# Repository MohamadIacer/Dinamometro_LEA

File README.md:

# Dinamometro_LEA
Repositório de desenvolvimento do sistema de dinamometria para turbinas em escala, utilizado pelo Laboratório de Energia e Ambiente da Universidade de Brasília.

Link com arquivos SolidWorks da montagem mecânica e peças individuais: https://1drv.ms/u/c/2880bb215aad6797/IQDlmrM-lfSOQbhDQPYtA1VkAWzMAm86arUpSsEFtpBo3BE?e=ooj1fM

Link com PDF do relatório da última iteração de desenvolvimento: https://1drv.ms/b/c/2880bb215aad6797/IQATOKx8Zu7TSKCGMIeG2nDvAc81WT-9CV8OO6a27Ivx5ow?e=Kimnmw

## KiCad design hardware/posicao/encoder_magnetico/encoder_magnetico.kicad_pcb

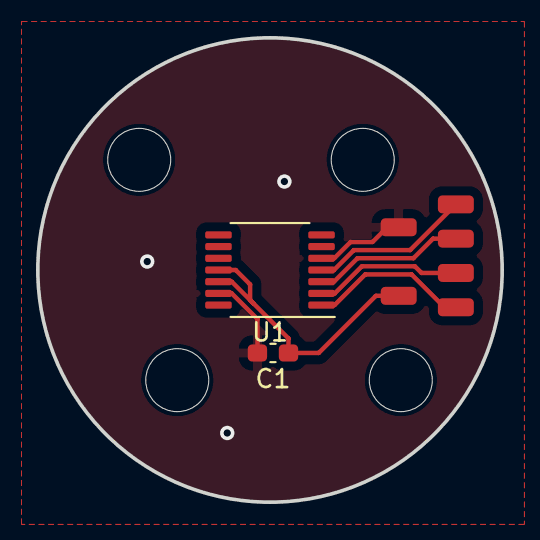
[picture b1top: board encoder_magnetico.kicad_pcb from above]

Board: 2 copper layers, 25.8 x 25.8 mm, 12 parts (0 on the bottom side), 6 nets.

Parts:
3V3: Conn_01x01; SolderWirePad_1x01_SMD_1x2mm
C1: 100nF; C_0603_1608Metric_Pad1.08x0.95mm_HandSolder
CK: Conn_01x01; SolderWirePad_1x01_SMD_1x2mm
CS: Conn_01x01; SolderWirePad_1x01_SMD_1x2mm
GND: Conn_01x01; SolderWirePad_1x01_SMD_1x2mm
H1, H2, H3, H4: MountingHole; MountingHole_3.5mm
MI: Conn_01x01; SolderWirePad_1x01_SMD_1x2mm
MO: Conn_01x01; SolderWirePad_1x01_SMD_1x2mm
U1: AS5047D; TSSOP-14_4.4x5mm_P0.65mm

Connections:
3v3: 3V3.1, C1.1, U1.11 (VDD), U1.12 (VDD3V3)
CLK: CK.1, U1.2 (CLK)
CS: CS.1, U1.1 (~CS)
GND: C1.2, GND.1, U1.5 (TST), U1.13 (GND)
MISO: MI.1, U1.3 (MISO)
MOSI: MO.1, U1.4 (MOSI)

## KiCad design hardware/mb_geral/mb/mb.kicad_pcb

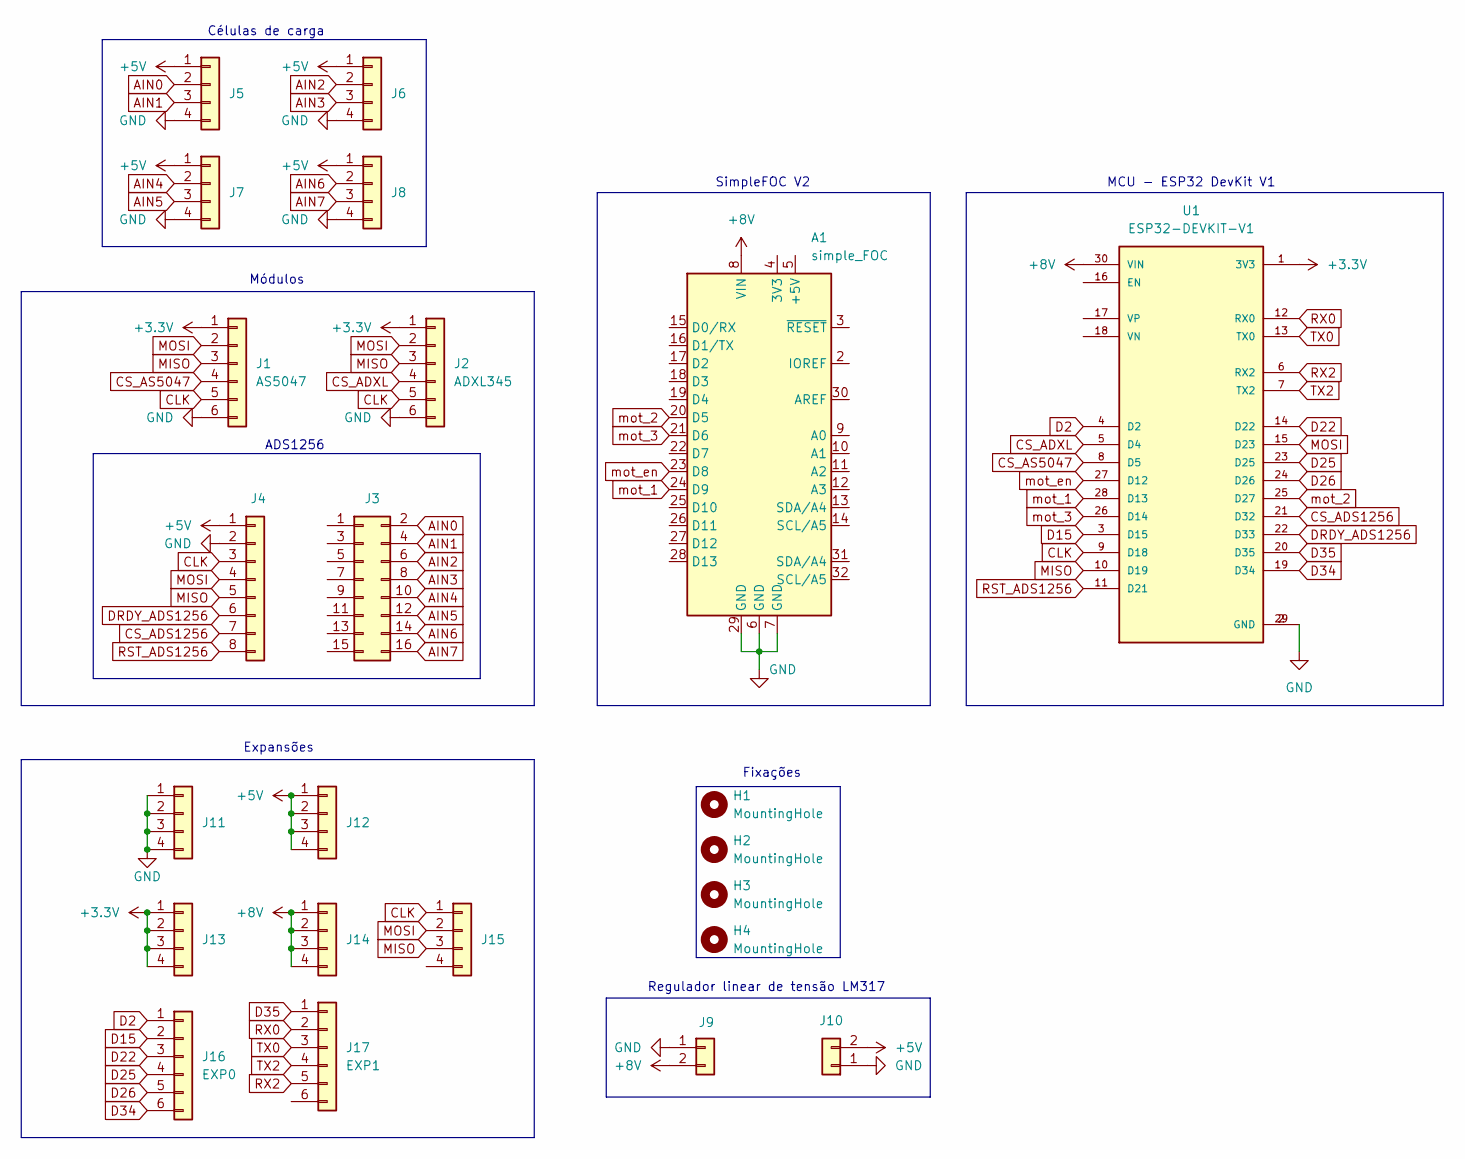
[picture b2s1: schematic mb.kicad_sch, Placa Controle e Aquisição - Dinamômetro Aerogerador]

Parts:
A1: simple_FOC; Arduino_UNO_R3
H1, H2, H3, H4: MountingHole; MountingHole_4mm
J1: AS5047; PinHeader_1x06_P2.54mm_Vertical
J2: ADXL345; PinHeader_1x06_P2.54mm_Vertical
J3: Conn_02x08_Top_Bottom; PinHeader_2x08_P2.54mm_Vertical
J4: Conn_01x08; PinHeader_1x08_P2.54mm_Vertical
J5, J6, J7, J8, J11, J12, J13, J14, J15: Conn_01x04; PinHeader_1x04_P2.54mm_Vertical
J9, J10: Conn_01x02; TerminalBlock_bornier-2_P5.08mm
J16: EXP0; PinHeader_1x06_P2.54mm_Vertical
J17: EXP1; PinHeader_1x06_P2.54mm_Vertical
U1: ESP32-DEVKIT-V1; MODULE_ESP32_DEVKIT_V1; PARTREV N/A

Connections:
+3.3V: J1.1, J2.1, J13.1, J13.2, J13.3, J13.4, U1.1 (3V3)
+5V: J4.1, J5.1, J6.1, J7.1, J8.1, J10.2, J12.1, J12.2, J12.3, J12.4
+8V: A1.8 (VIN), J9.2, J14.1, J14.2, J14.3, J14.4, U1.30 (VIN)
AIN0: J3.2, J5.2
AIN1: J3.4, J5.3
AIN2: J3.6, J6.2
AIN3: J3.8, J6.3
AIN4: J3.10, J7.2
AIN5: J3.12, J7.3
AIN6: J3.14, J8.2
AIN7: J3.16, J8.3
CLK: J1.5, J2.5, J4.3, J15.1, U1.9 (D18)
CS_ADS1256: J4.7, U1.21 (D32)
CS_ADXL: J2.4, U1.5 (D4)
CS_AS5047: J1.4, U1.8 (D5)
D2: J16.1, U1.4 (D2)
D15: J16.2, U1.3 (D15)
D22: J16.3, U1.14 (D22)
D25: J16.4, U1.23 (D25)
D26: J16.5, U1.24 (D26)
D34: J16.6, U1.19 (D34)
D35: J17.1, U1.20 (D35)
DRDY_ADS1256: J4.6, U1.22 (D33)
GND: A1.6 (GND), A1.7 (GND), A1.29 (GND), J1.6, J2.6, J4.2, J5.4, J6.4, J7.4, J8.4, J9.1, J10.1, J11.1, J11.2, J11.3, J11.4, U1.2 (GND), U1.29 (GND)
MISO: J1.3, J2.3, J4.5, J15.3, U1.10 (D19)
MOSI: J1.2, J2.2, J4.4, J15.2, U1.15 (D23)
RST_ADS1256: J4.8, U1.11 (D21)
RX0: J17.2, U1.12 (RX0)
RX2: J17.5, U1.6 (RX2)
TX0: J17.3, U1.13 (TX0)
TX2: J17.4, U1.7 (TX2)
mot_1: A1.24 (D9), U1.28 (D13)
mot_2: A1.20 (D5), U1.25 (D27)
mot_3: A1.21 (D6), U1.26 (D14)
mot_en: A1.23 (D8), U1.27 (D12)

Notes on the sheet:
Células de carga
Expansões
SimpleFOC V2
Módulos
ADS1256
Fixações
MCU - ESP32 DevKit V1
Regulador linear de tensão LM317

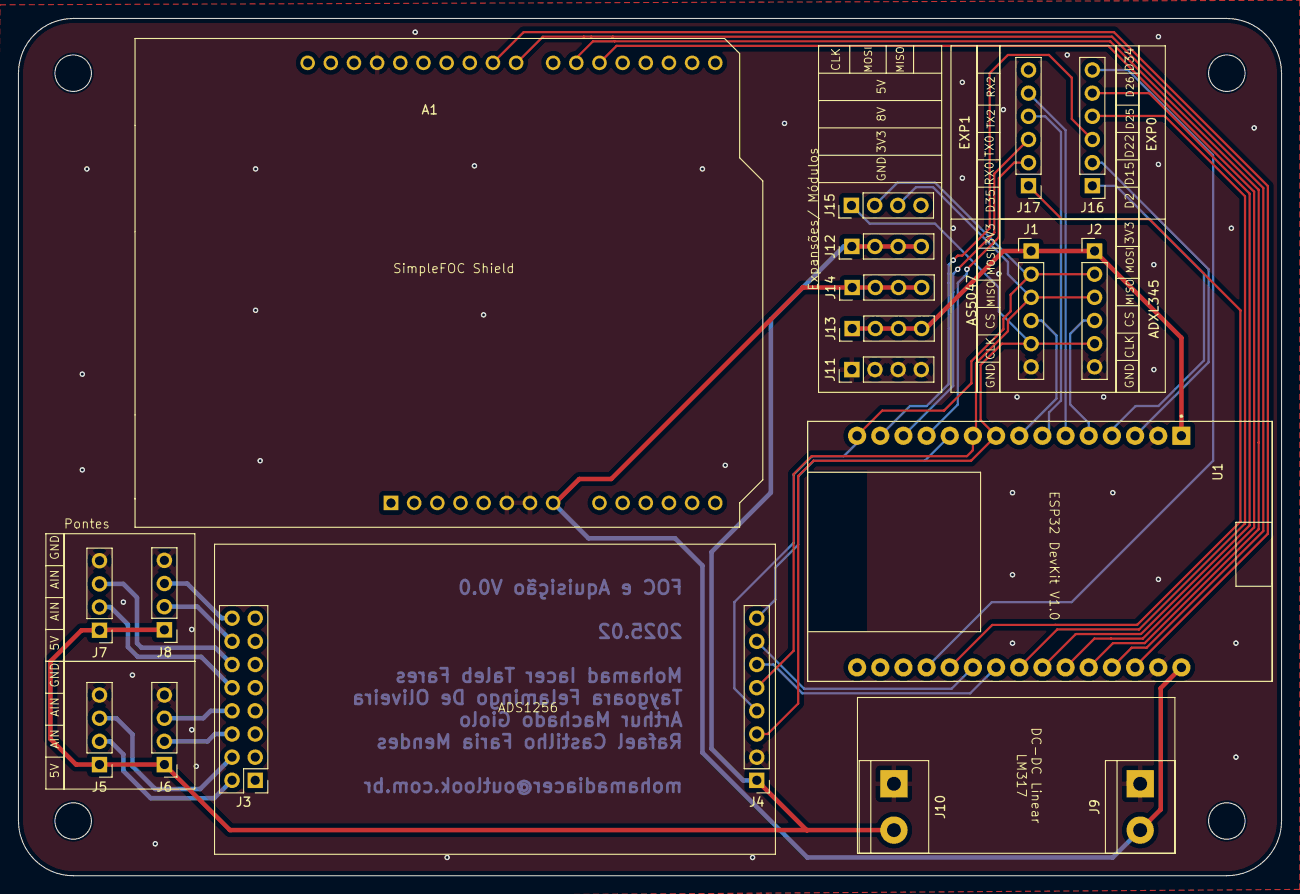
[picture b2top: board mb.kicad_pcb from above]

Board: 2 copper layers, 138.5 x 94.0 mm, 23 parts (0 on the bottom side), 35 nets.

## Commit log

2025-12-02 Add hardware directory
2025-12-02 Add .gitkeep to hardware directory
2025-12-02 Update hardware
2025-12-02 Update README with SolidWorks files link
    Added link to SolidWorks files for mechanical assembly.
2025-12-02 Add link to PDF report of latest development iteration
